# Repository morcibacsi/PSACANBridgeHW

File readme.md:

# PSA CAN protocol bridge (hardware)

### What is it ?
This is the hardware needed for my [PSA CAN protocol bridge][psacanbridge] software.

The files were created with KiCad

The main branch contains only this readme file as the boards themselves are pretty much different and having a continuous history does not really make sense. 
So every revision has its own branch. They are in the state as I sent them to the manufacturing company.

💡 **I recommmend using the latest revision as that contains fixes for encountered problems in previous versions. Also the software is kept in-line with the latest hardware revision, so it is possible that newer software releases don't work properly on the older revisions.**

### Available revisions

- [Rev 1.1][version_11]
- [Rev 1.3][version_13]
- [Rev 1.4][version_14]
- [Rev 1.5][version_15]

[version_11]: https://github.com/morcibacsi/PSACANBridgeHW/tree/v1.1
[version_13]: https://github.com/morcibacsi/PSACANBridgeHW/tree/v1.3
[version_14]: https://github.com/morcibacsi/PSACANBridgeHW/tree/v1.4
[version_15]: https://github.com/morcibacsi/PSAVanCanBridgeHW/tree/v1.5
[psacanbridge]: https://github.com/morcibacsi/PSACANBridge

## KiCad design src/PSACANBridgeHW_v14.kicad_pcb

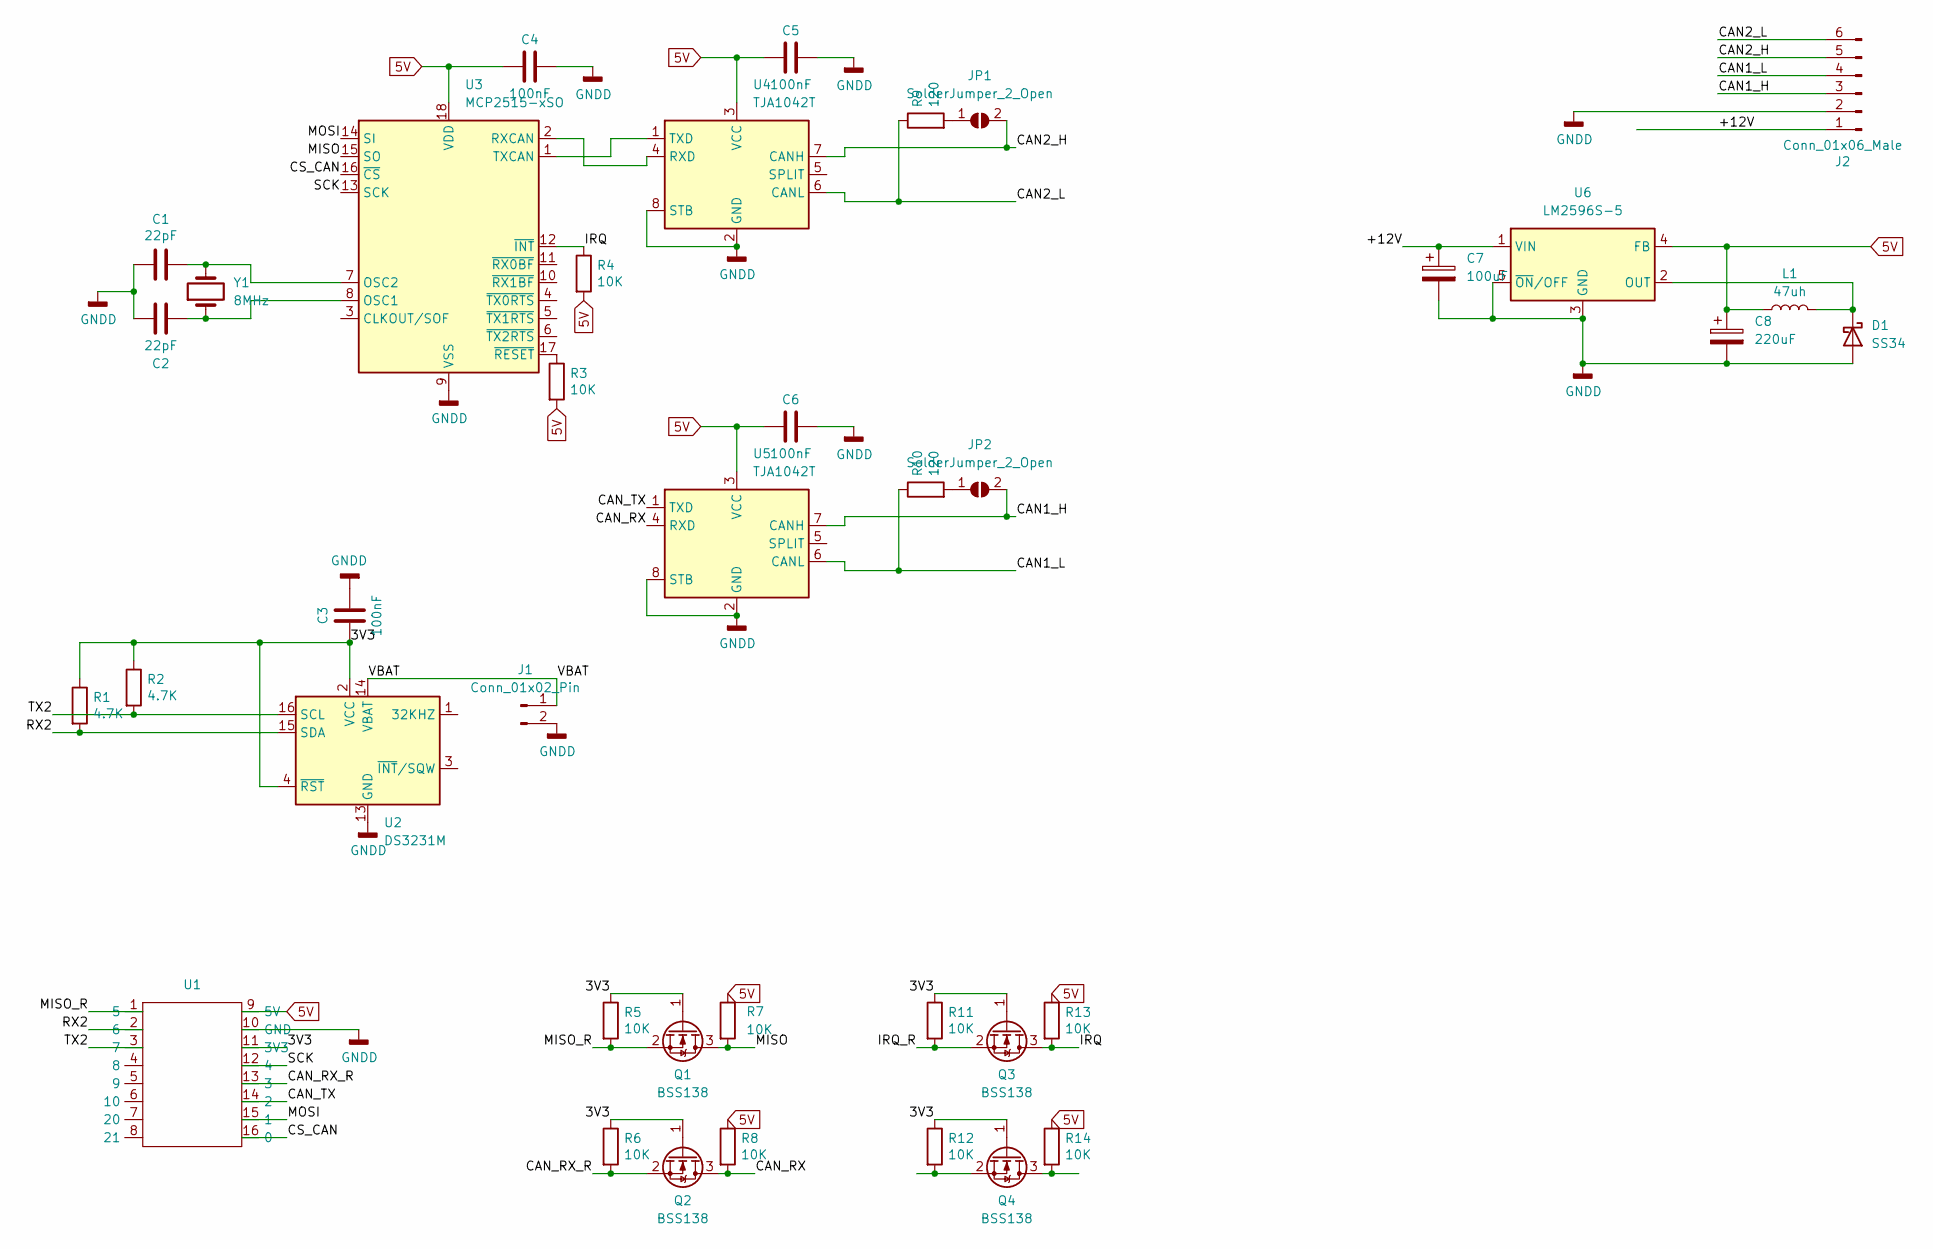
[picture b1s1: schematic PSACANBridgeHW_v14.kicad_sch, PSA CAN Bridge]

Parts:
C1, C2: 22pF; C_0603_1608Metric_Pad1.08x0.95mm_HandSolder; LCSC C1653
C3, C4, C5, C6: 100nF; C_0603_1608Metric_Pad1.08x0.95mm_HandSolder; LCSC C14663
C7: 100uF; CP_Radial_D6.3mm_P2.50mm
C8: 220uF; CP_Radial_D6.3mm_P2.50mm
D1: SS34; D_SMA; LCSC C7420365
J1: Conn_01x02_Pin; DS3231_BatteryHolder
J2: Conn_01x06_Male; JST_EH_S6B-EH_1x06_P2.50mm_Horizontal
JP1, JP2: SolderJumper_2_Open; SolderJumper-2_P1.3mm_Open_Pad1.0x1.5mm
L1: 47uh; L_12x12mm_H8mm; LCSC C167265
Q1, Q2, Q3, Q4: BSS138; SOT-23; LCSC C112239
R1, R2: 4.7K; R_0603_1608Metric_Pad0.98x0.95mm_HandSolder; LCSC C25999
R3, R4, R5, R6, R7, R8, R11, R12, R13, R14: 10K; R_0603_1608Metric_Pad0.98x0.95mm_HandSolder; LCSC C25804
R9, R10: 120; R_0603_1608Metric_Pad0.98x0.95mm_HandSolder
U1: ESP32_c3_supermini
U2: DS3231M; SOIC-16W_7.5x10.3mm_P1.27mm; JLCPCB Rotation Offset -90
U3: MCP2515-xSO; SOIC-18W_7.5x11.6mm_P1.27mm; LCSC C12368
U4, U5: TJA1042T; SOIC-8_3.9x4.9mm_P1.27mm; LCSC C6952
U6: LM2596S-5; TO-263-5_TabPin3; LCSC C347421
Y1: 8MHz; Crystal_SMD_5032-2Pin_5.0x3.2mm; LCSC C115962

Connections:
5V: C4.2, C5.2, C6.2, C8.1, L1.1, R3.2, R4.2, R7.1, R8.1, R13.1, R14.1, U1.9 (5V), U3.18 (VDD), U4.3 (VCC), U5.3 (VCC), U6.4 (FB)
/3V3: C3.2, Q1.1 (G), Q2.1 (G), Q3.1 (G), Q4.1 (G), R1.1, R2.1, R5.1, R6.1, R11.1, R12.1, U1.11 (3V3), U2.2 (VCC), U2.4 (~RST)
/+12V: C7.1, J2.1, U6.1 (VIN)
/CAN1_H: J2.3, JP2.2 (B), U5.7 (CANH)
/CAN1_L: J2.4, R10.1, U5.6 (CANL)
/CAN2_H: J2.5, JP1.2 (B), U4.7 (CANH)
/CAN2_L: J2.6, R9.1, U4.6 (CANL)
/CAN_RX: Q2.3 (D), R8.2, U5.4 (RXD)
/CAN_RX_R: Q2.2 (S), R6.2, U1.13 (3)
/CAN_TX: U1.14 (2), U5.1 (TXD)
/CS_CAN: U1.16 (0), U3.16 (~CS)
/IRQ: Q3.3 (D), R4.1, R13.2, U3.12 (~INT)
/IRQ_R: Q3.2 (S), R11.2
/MISO: Q1.3 (D), R7.2, U3.15 (SO)
/MISO_R: Q1.2 (S), R5.2, U1.1 (5)
/MOSI: U1.15 (1), U3.14 (SI)
/RX2: R1.2, U1.2 (6), U2.15 (SDA)
/SCK: U1.12 (4), U3.13 (SCK)
/TX2: R2.2, U1.3 (7), U2.16 (SCL)
/VBAT: J1.1, U2.14 (VBAT)
GNDD: C1.2, C2.2, C3.1, C4.1, C5.1, C6.1, C7.2, C8.2, D1.2 (A), J1.2, J2.2, U1.10 (GND), U2.5 (GND), U2.6 (GND), U2.7 (GND), U2.8 (GND), U2.9 (GND), U2.10 (GND), U2.11 (GND), U2.12 (GND), U2.13 (GND), U3.9 (VSS), U4.2 (GND), U4.8 (STB), U5.2 (GND), U5.8 (STB), U6.3 (GND), U6.5 (~ON/OFF)
unnamed: D1.1 (K), L1.2, U6.2 (OUT)
unnamed: JP1.1 (A), R9.2
unnamed: JP2.1 (A), R10.2
unnamed: Q4.3 (D), R14.2
unnamed: Q4.2 (S), R12.2
unnamed: C2.1, U3.8 (OSC1), Y1.1
unnamed: C1.1, U3.7 (OSC2), Y1.2
unnamed: U3.2 (RXCAN), U4.4 (RXD)
unnamed: U3.1 (TXCAN), U4.1 (TXD)
unnamed: R3.1, U3.17 (~RESET)

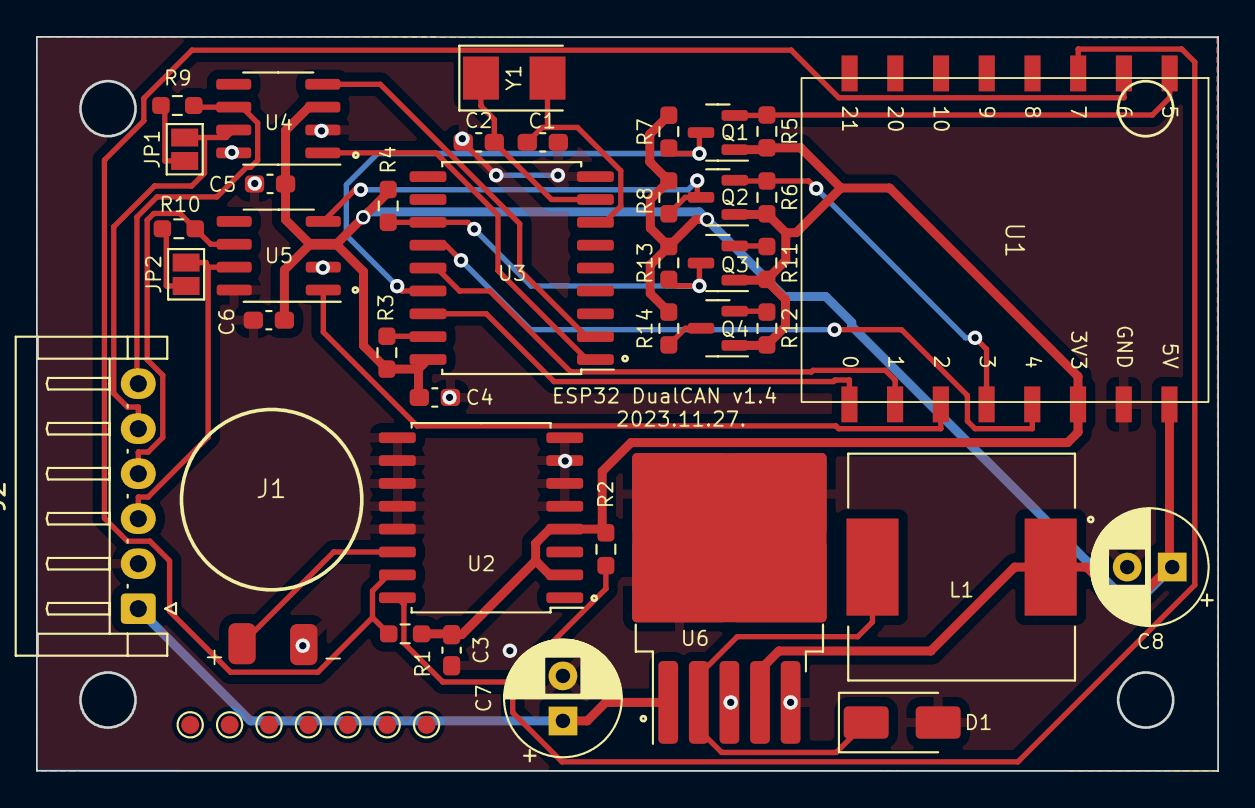
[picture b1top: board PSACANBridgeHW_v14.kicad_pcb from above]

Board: 2 copper layers, 65.6 x 40.7 mm, 39 parts (0 on the bottom side), 31 nets.

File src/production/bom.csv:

Designator,Footprint,Quantity,Value,LCSC Part #
"C1, C2",0603,2,22pF,C1653
"C3, C4, C5, C6",0603,4,100nF,C14663
C7,CP_Radial_D6.3mm_P2.50mm,1,100uF,
C8,CP_Radial_D6.3mm_P2.50mm,1,220uF,
D1,D_SMA,1,SS34,C7420365
J1,DS3231_BatteryHolder,1,Conn_01x02_Pin,
J2,JST_EH_S6B-EH_1x06_P2.50mm_Horizontal,1,Conn_01x06_Male,
"JP1, JP2",SolderJumper-2_P1.3mm_Open_Pad1.0x1.5mm,2,SolderJumper_2_Open,
L1,L_12x12mm_H8mm,1,47uh,C167265
"Q1, Q2, Q3, Q4",SOT-23,4,BSS138,C112239
"R1, R2",0603,2,4.7K,C25999
"R10, R9",0603,2,120,
"R11, R12, R13, R14, R3, R4, R5, R6, R7, R8",0603,10,10K,C25804
U1,ESP32_c3_supermini,1,~,
U2,SOIC-16W_7.5x10.3mm_P1.27mm,1,DS3231M,
U3,SOIC-18W_7.5x11.6mm_P1.27mm,1,MCP2515-xSO,C12368
"U4, U5",SOIC-8_3.9x4.9mm_P1.27mm,2,TJA1042T,C6952
U6,TO-263-5_TabPin3,1,LM2596S-5,C347421
Y1,Crystal_SMD_5032-2Pin_5.0x3.2mm,1,8MHz,C115962

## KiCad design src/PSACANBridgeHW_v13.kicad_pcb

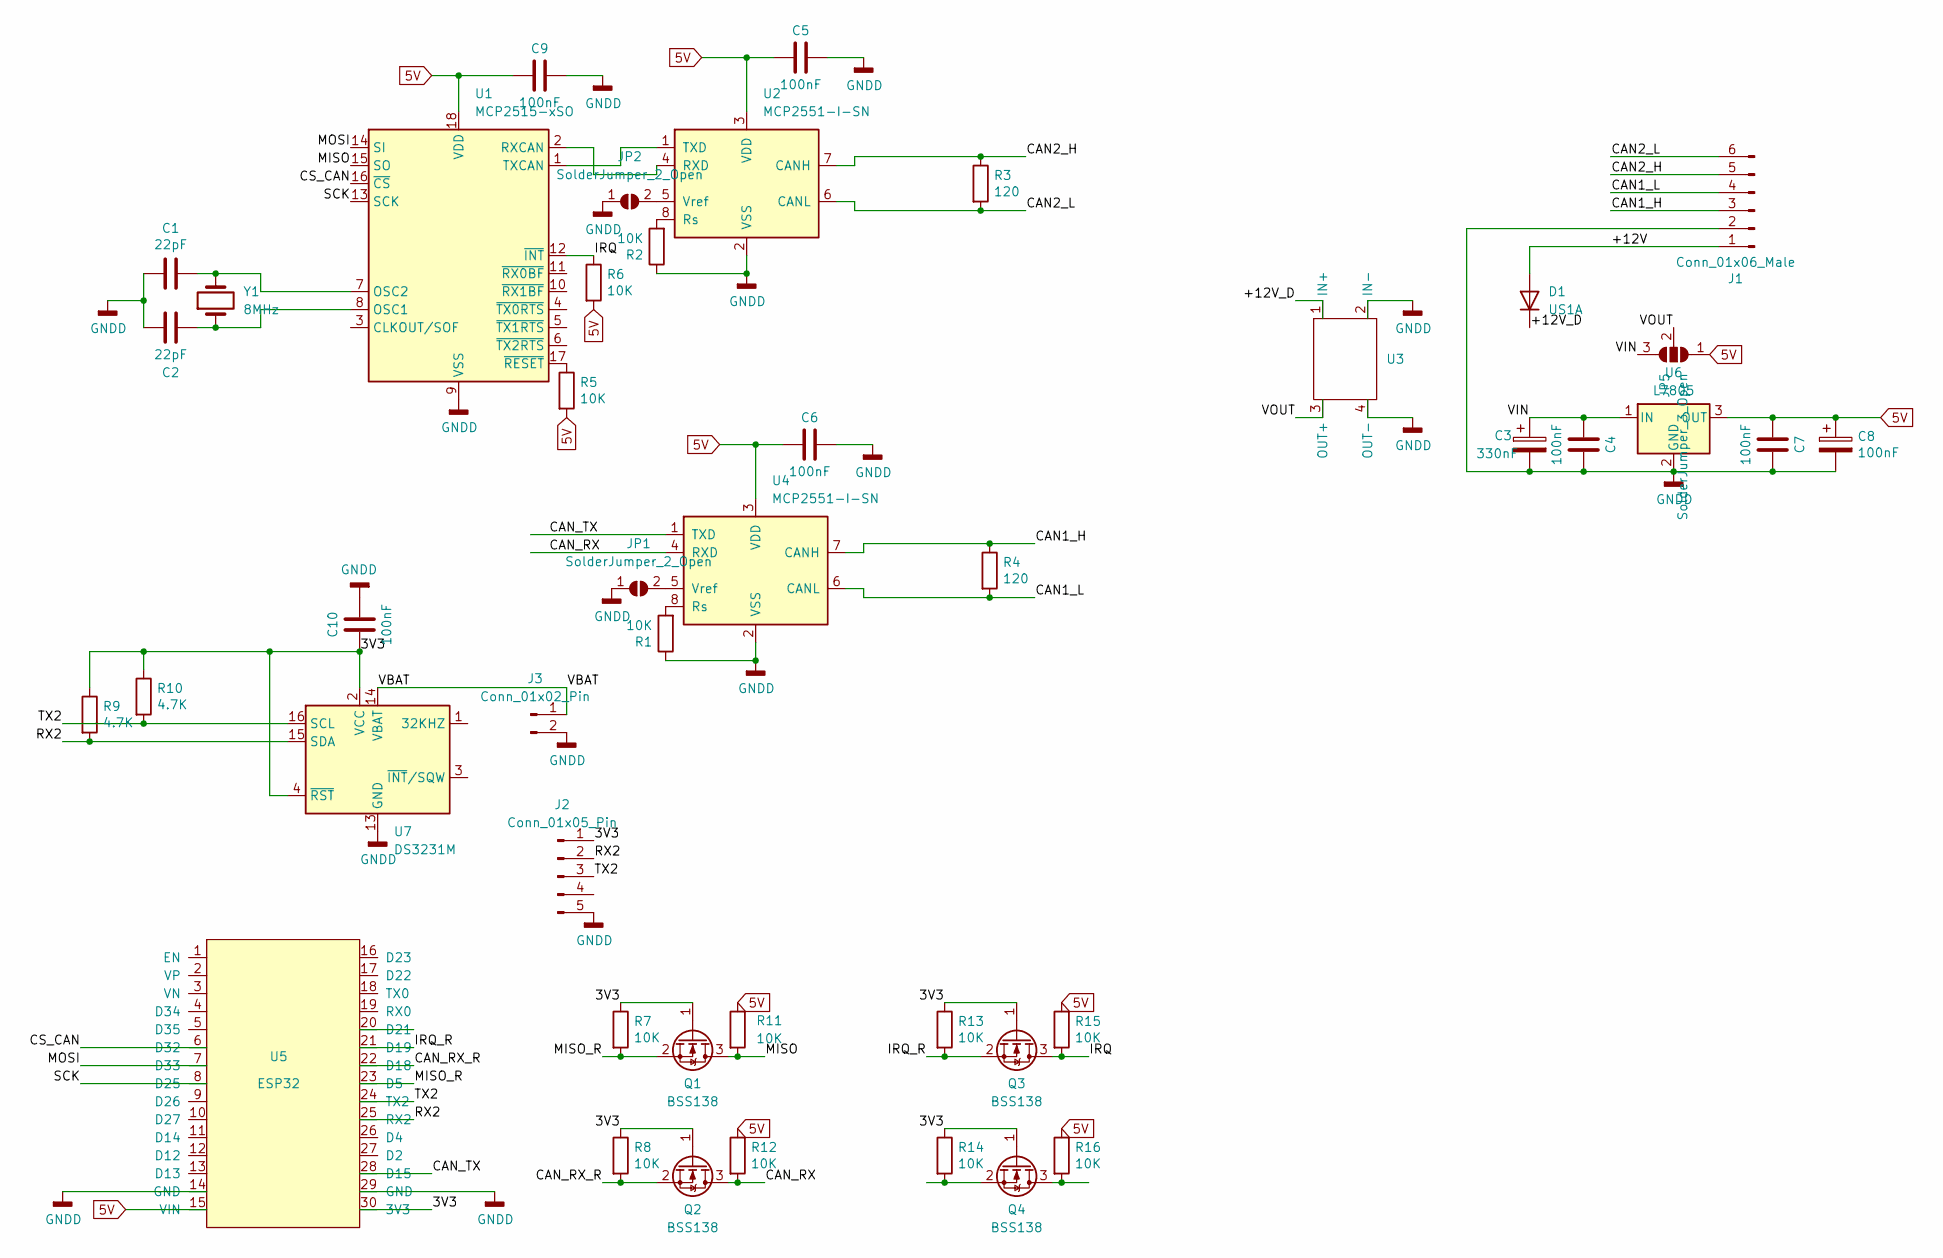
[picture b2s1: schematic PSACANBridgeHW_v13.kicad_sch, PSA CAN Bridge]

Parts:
C1, C2: 22pF; C_0603_1608Metric_Pad1.08x0.95mm_HandSolder; LCSC C1653
C3: 330nF; CP_Radial_D4.0mm_P2.00mm
C4, C5, C6, C7, C9, C10: 100nF; C_0603_1608Metric_Pad1.08x0.95mm_HandSolder; LCSC C14663
C8: 100nF; CP_Radial_D4.0mm_P2.00mm
D1: US1A; D_SMA; LCSC C95872
J1: Conn_01x06_Male; JST_EH_S6B-EH_1x06_P2.50mm_Horizontal
J2: Conn_01x05_Pin; PinHeader_1x05_P2.54mm_Vertical
J3: Conn_01x02_Pin; DS3231_BatteryHolder
JP1, JP2: SolderJumper_2_Open; SolderJumper-2_P1.3mm_Open_Pad1.0x1.5mm
JP5: SolderJumper_3_Open; SolderJumper-3_P1.3mm_Open_Pad1.0x1.5mm
Q1, Q2, Q3, Q4: BSS138; SOT-23; LCSC C112239
R1, R2, R5, R6, R7, R8, R11, R12, R13, R14, R15, R16: 10K; R_0603_1608Metric_Pad0.98x0.95mm_HandSolder; LCSC C25804
R3, R4: 120; R_0603_1608Metric_Pad0.98x0.95mm_HandSolder
R9, R10: 4.7K; R_0603_1608Metric_Pad0.98x0.95mm_HandSolder; LCSC C25999
U1: MCP2515-xSO; SOIC-18W_7.5x11.6mm_P1.27mm; LCSC C12368
U2, U4: MCP2551-I-SN; SOIC-8_3.9x4.9mm_P1.27mm; LCSC C49558
U3: StepDown_MP1584_shield
U5: ESP32; ESP32_shield
U6: L7805; TO-252-2
U7: DS3231M; SOIC-16W_7.5x10.3mm_P1.27mm; JLCPCB Rotation Offset -90
Y1: 8MHz; Crystal_SMD_5032-2Pin_5.0x3.2mm; LCSC C115962

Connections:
5V: C5.2, C6.2, C7.2, C8.1, C9.2, JP5.1 (A), R5.2, R6.2, R11.1, R12.1, R15.1, R16.1, U1.18 (VDD), U2.3 (VDD), U4.3 (VDD), U5.15 (VIN), U6.3 (OUT)
/3V3: C10.2, J2.1, Q1.1 (G), Q2.1 (G), Q3.1 (G), Q4.1 (G), R7.1, R8.1, R9.1, R10.1, R13.1, R14.1, U5.30 (3V3), U7.2 (VCC), U7.4 (~RST)
/+12V: D1.2 (A), J1.1
/+12V_D: D1.1 (K), U3.1 (IN+)
/CAN1_H: J1.3, R4.1, U4.7 (CANH)
/CAN1_L: J1.4, R4.2, U4.6 (CANL)
/CAN2_H: J1.5, R3.1, U2.7 (CANH)
/CAN2_L: J1.6, R3.2, U2.6 (CANL)
/CAN_RX: Q2.3 (D), R12.2, U4.4 (RXD)
/CAN_RX_R: Q2.2 (S), R8.2, U5.22 (D18)
/CAN_TX: U4.1 (TXD), U5.28 (D15)
/CS_CAN: U1.16 (~CS), U5.6 (D32)
/IRQ: Q3.3 (D), R6.1, R15.2, U1.12 (~INT)
/IRQ_R: Q3.2 (S), R13.2, U5.21 (D19)
/MISO: Q1.3 (D), R11.2, U1.15 (SO)
/MISO_R: Q1.2 (S), R7.2, U5.23 (D5)
/MOSI: U1.14 (SI), U5.7 (D33)
/RX2: J2.2, R9.2, U5.25 (RX2), U7.15 (SDA)
/SCK: U1.13 (SCK), U5.8 (D25)
/TX2: J2.3, R10.2, U5.24 (TX2), U7.16 (SCL)
/VBAT: J3.1, U7.14 (VBAT)
/VIN: C3.1, C4.2, JP5.3 (B), U6.1 (IN)
/VOUT: JP5.2 (C), U3.3 (OUT+)
GNDD: C1.2, C2.2, C3.2, C4.1, C5.1, C6.1, C7.1, C8.2, C9.1, C10.1, J1.2, J2.5, J3.2, JP1.1 (A), JP2.1 (A), R1.1, R2.1, U1.9 (VSS), U2.2 (VSS), U3.2 (IN-), U3.4 (OUT-), U4.2 (VSS), U5.14 (GND), U5.29 (GND), U6.2 (GND), U7.5 (GND), U7.6 (GND), U7.7 (GND), U7.8 (GND), U7.9 (GND), U7.10 (GND), U7.11 (GND), U7.12 (GND), U7.13 (GND)
unnamed: JP1.2 (B), U4.5 (Vref)
unnamed: JP2.2 (B), U2.5 (Vref)
unnamed: Q4.3 (D), R16.2
unnamed: Q4.2 (S), R14.2
unnamed: C2.1, U1.8 (OSC1), Y1.1
unnamed: C1.1, U1.7 (OSC2), Y1.2
unnamed: U1.2 (RXCAN), U2.4 (RXD)
unnamed: U1.1 (TXCAN), U2.1 (TXD)
unnamed: R5.1, U1.17 (~RESET)
unnamed: R2.2, U2.8 (Rs)
unnamed: R1.2, U4.8 (Rs)

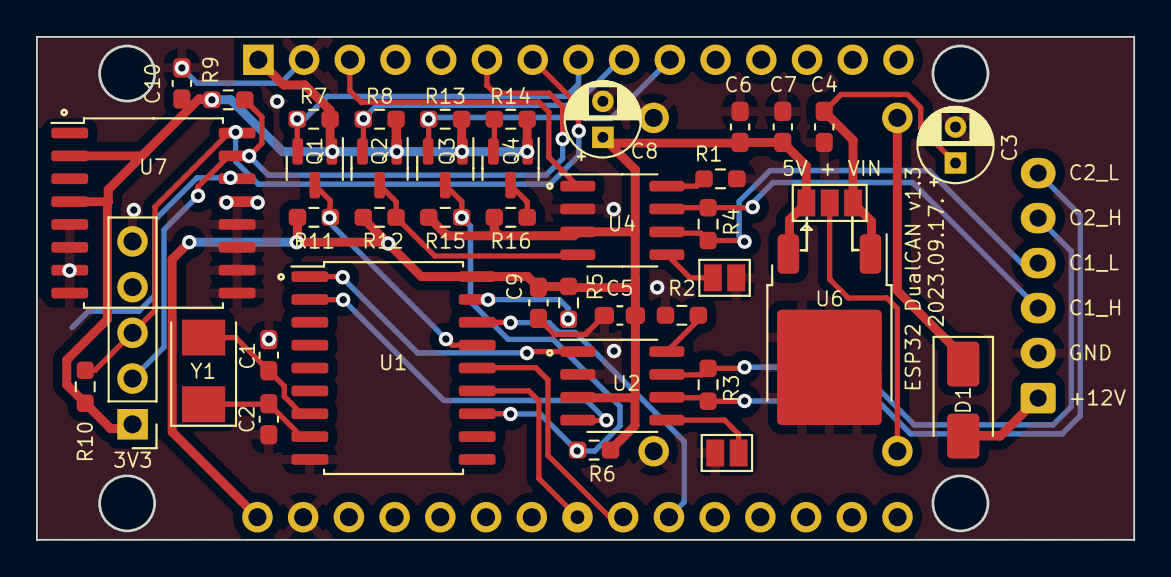
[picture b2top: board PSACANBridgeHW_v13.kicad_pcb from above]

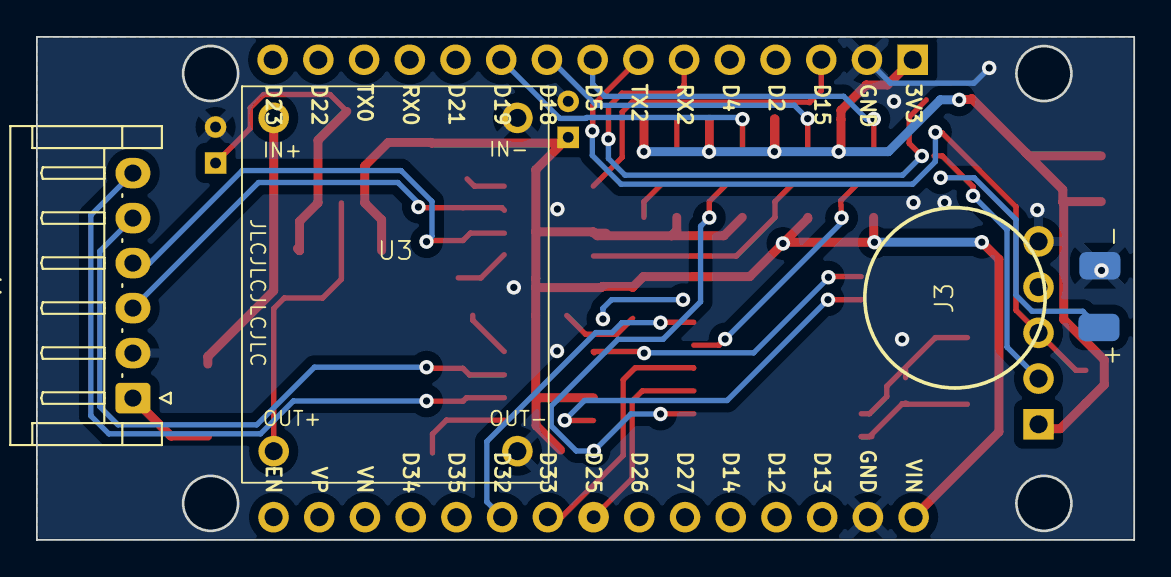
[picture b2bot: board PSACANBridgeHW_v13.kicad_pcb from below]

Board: 2 copper layers, 60.9 x 27.9 mm, 45 parts (4 on the bottom side), 35 nets.

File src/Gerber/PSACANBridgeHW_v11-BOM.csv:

Comment,Designator,Footprint,LCSC part number
"Buzzer","BZ1","Buzzer_Beeper:MagneticBuzzer_Kingstate_KCG0601",""
"22pF","C1,C2","Capacitor_SMD:C_0603_1608Metric_Pad1.05x0.95mm_HandSolder","","C1653"
"33uF","C3","Capacitor_Tantalum_SMD:CP_EIA-3528-21_Kemet-B_Pad1.50x2.35mm_HandSolder","","C10785"
"100nF","C6,C5,C4,C7,C9","Capacitor_SMD:C_0603_1608Metric_Pad1.05x0.95mm_HandSolder","","C14663"
"47uF","C8","Capacitor_Tantalum_SMD:CP_EIA-3528-21_Kemet-B_Pad1.50x2.35mm_HandSolder","","C123253"
"D_ALT","D1","Diode_SMD:D_SMA","","C95872"
"Conn_01x06_Male","J1","Connector_JST:JST_EH_S06B-EH_1x06_P2.50mm_Horizontal",""
"Conn_01x03_Male","J2","Connector_PinSocket_2.54mm:PinSocket_1x03_P2.54mm_Vertical",""
"Conn_01x04_Male","J3","Connector_PinHeader_2.54mm:PinHeader_1x04_P2.54mm_Vertical",""
"PN2222A","Q1","Package_TO_SOT_THT:TO-92_Inline",""
"BSS138","Q4,Q5,Q2,Q3","Package_TO_SOT_SMD:SOT-23","","C112239"
"10K","R13,R15,R14,R16,R7,R11,R8,R12,R5,R6","Resistor_SMD:R_0603_1608Metric_Pad1.05x0.95mm_HandSolder","","C25804"
"2.2K","R2,R1","Resistor_SMD:R_0603_1608Metric_Pad1.05x0.95mm_HandSolder","","C4190"
"120","R3,R4","Resistor_SMD:R_0603_1608Metric_Pad1.05x0.95mm_HandSolder",""
"MCP2515-xSO","U1","Package_SO:SOIC-18W_7.5x11.6mm_P1.27mm","","C12368"
"TJA1042T","U3,U2","Package_SO:SOIC-8_3.9x4.9mm_P1.27mm","","C6951"
"ESP32","U5","PSACANBridgeHW_v11:ESP32_shield",""
"LM7805_TO220","U6","Package_TO_SOT_SMD:TO-252-2",""
"8MHz","Y1","Crystal:Crystal_HC49-4H_Vertical",""

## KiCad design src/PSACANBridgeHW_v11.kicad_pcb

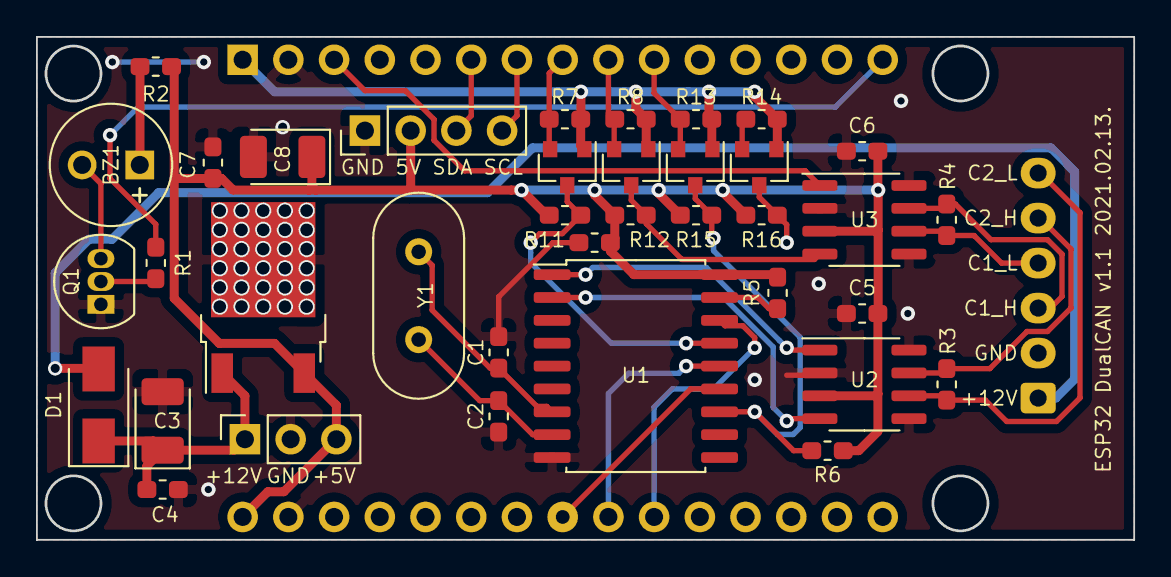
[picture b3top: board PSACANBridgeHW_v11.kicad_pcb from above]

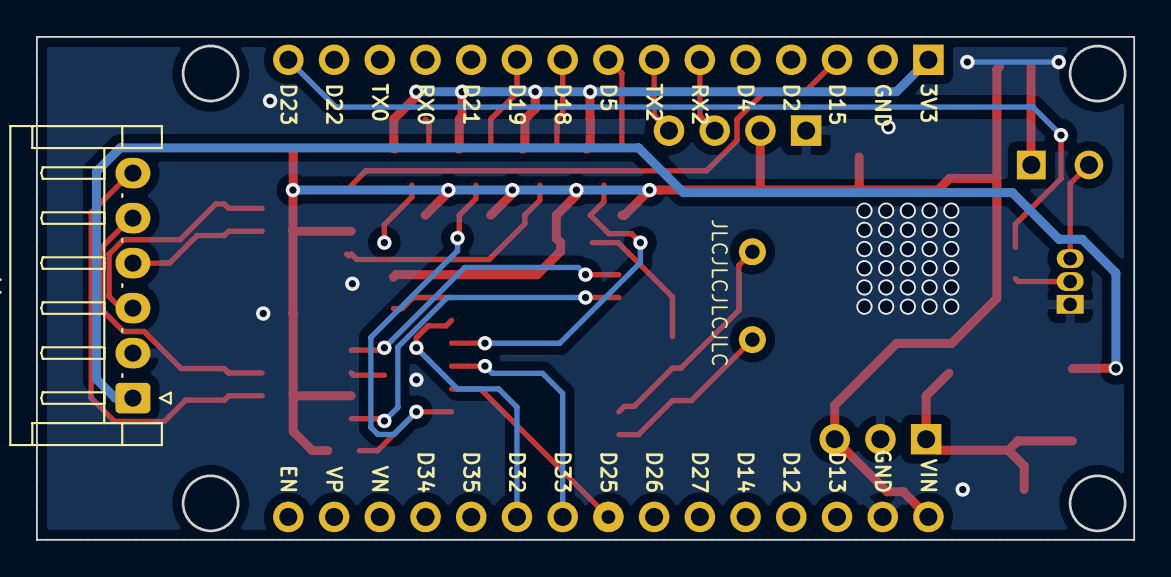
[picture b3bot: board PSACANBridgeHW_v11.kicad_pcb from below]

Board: 2 copper layers, 60.9 x 27.9 mm, 39 parts (2 on the bottom side), 32 nets.

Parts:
BZ1: Buzzer; MagneticBuzzer_Kingstate_KCG0601
C1, C2: 22pF; C_0603_1608Metric_Pad1.05x0.95mm_HandSolder
C3: 33uF; CP_EIA-3528-21_Kemet-B_Pad1.50x2.35mm_HandSolder
C4, C5, C6, C7, C9: 100nF; C_0603_1608Metric_Pad1.05x0.95mm_HandSolder
C8: 47uF; CP_EIA-3528-21_Kemet-B_Pad1.50x2.35mm_HandSolder
D1: D_ALT; D_SMA
J1: Conn_01x06_Male; JST_EH_S06B-EH_1x06_P2.50mm_Horizontal
J2: Conn_01x03_Male; PinSocket_1x03_P2.54mm_Vertical
J3: Conn_01x04_Male; PinHeader_1x04_P2.54mm_Vertical
Q1: PN2222A; TO-92_Inline
Q2, Q3, Q4, Q5: BSS138; SOT-23
R1, R2: 2.2K; R_0603_1608Metric_Pad1.05x0.95mm_HandSolder
R3, R4: 120; R_0603_1608Metric_Pad1.05x0.95mm_HandSolder
R5, R6, R7, R8, R11, R12, R13, R14, R15, R16: 10K; R_0603_1608Metric_Pad1.05x0.95mm_HandSolder
U1: MCP2515-xSO; SOIC-18W_7.5x11.6mm_P1.27mm
U2, U3: TJA1042T; SOIC-8_3.9x4.9mm_P1.27mm
U5: ESP32; ESP32_shield
U6: LM7805_TO220; TO-252-2
Y1: 8MHz; Crystal_HC49-4H_Vertical

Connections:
5V: C5.2, C6.2, C7.2, C8.1, C9.2, J2.3, J3.2, R2.2, R5.2, R6.2, R11.1, R12.1, R15.1, R16.1, U1.18, U2.3, U3.3, U5.15, U6.3
/3V3: Q2.1, Q3.1, Q4.1, Q5.1, R7.1, R8.1, R13.1, R14.1, U5.30
/+12V: D1.2, J1.1
/+12V_D: C3.1, C4.2, D1.1, J2.1, U6.1
/BZ: R1.2, U5.16
/CAN1_H: J1.3, R4.1, U3.7
/CAN1_L: J1.4, R4.2, U3.6
/CAN2_H: J1.5, R3.1, U2.7
/CAN2_L: J1.6, R3.2, U2.6
/CAN_RX: Q3.3, R12.2, U3.4
/CAN_RX_R: Q3.2, R8.2, U5.22
/CAN_TX: U3.1, U5.28
/CS_CAN: U1.16, U5.6
/IRQ: Q4.3, R6.1, R15.2, U1.12
/IRQ_R: Q4.2, R13.2, U5.21
/MISO: Q2.3, R11.2, U1.15
/MISO_R: Q2.2, R7.2, U5.23
/MOSI: U1.14, U5.7
/RX2: J3.3, U5.25
/SCK: U1.13, U5.8
/TX2: J3.4, U5.24
GNDD: C1.2, C2.2, C3.2, C4.1, C5.1, C6.1, C7.1, C8.2, C9.1, J1.2, J2.2, J3.1, Q1.1, U1.9, U2.2, U2.5, U2.8, U3.2, U3.5, U3.8, U5.14, U5.29, U6.2
unnamed: BZ1.1, R2.1
unnamed: BZ1.2, Q1.3
unnamed: C1.1, U1.7, Y1.1
unnamed: C2.1, U1.8, Y1.2
unnamed: Q1.2, R1.1
unnamed: Q5.2, R14.2
unnamed: Q5.3, R16.2
unnamed: R5.1, U1.17
unnamed: U1.1, U2.1
unnamed: U1.2, U2.4

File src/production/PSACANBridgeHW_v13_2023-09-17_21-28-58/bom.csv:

Designator,Footprint,Quantity,Value,LCSC Part #
"C1, C2",0603,2,22pF,C1653
"C10, C4, C5, C6, C7, C9",0603,6,100nF,C14663
C3,CP_Radial_D4.0mm_P2.00mm,1,330nF,
C8,CP_Radial_D4.0mm_P2.00mm,1,100nF,
D1,D_SMA,1,US1A,C95872
J1,JST_EH_S6B-EH_1x06_P2.50mm_Horizontal,1,Conn_01x06_Male,
J2,PinHeader_1x05_P2.54mm_Vertical,1,Conn_01x05_Pin,
J3,DS3231_BatteryHolder,1,Conn_01x02_Pin,
"JP1, JP2",SolderJumper-2_P1.3mm_Open_Pad1.0x1.5mm,2,SolderJumper_2_Open,
JP5,SolderJumper-3_P1.3mm_Open_Pad1.0x1.5mm,1,SolderJumper_3_Open,
"Q1, Q2, Q3, Q4",SOT-23,4,BSS138,C112239
"R1, R11, R12, R13, R14, R15, R16, R2, R5, R6, R7, R8",0603,12,10K,C25804
"R10, R9",0603,2,4.7K,C25999
"R3, R4",0603,2,120,
U1,SOIC-18W_7.5x11.6mm_P1.27mm,1,MCP2515-xSO,C12368
"U2, U4",SOIC-8_3.9x4.9mm_P1.27mm,2,MCP2551-I-SN,C49558
U3,StepDown_MP1584_shield,1,~,
U5,ESP32_shield,1,ESP32,
U6,TO-252-2,1,L7805,
U7,SOIC-16W_7.5x10.3mm_P1.27mm,1,DS3231M,
Y1,Crystal_SMD_5032-2Pin_5.0x3.2mm,1,8MHz,C115962

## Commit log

2022-12-29 Added readme
2022-12-29 Added files
2022-12-29 Added link to Rev 1.1
2023-10-25 Added link to Rev 1.3
2024-01-30 Added link to Rev 1.4
